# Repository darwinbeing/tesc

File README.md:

VESC – Open Source ESC
=============

This the Hardware for my open source custom ESC.

[//]: # (Image References)
[image1]: design/PNGs/VESC_6_plus_top.png "MB Front"
[image2]: design/PNGs/VESC_6_plus_bottom.png "MB Back"

## 3D views
![alt text][image1]
![alt text][image2]

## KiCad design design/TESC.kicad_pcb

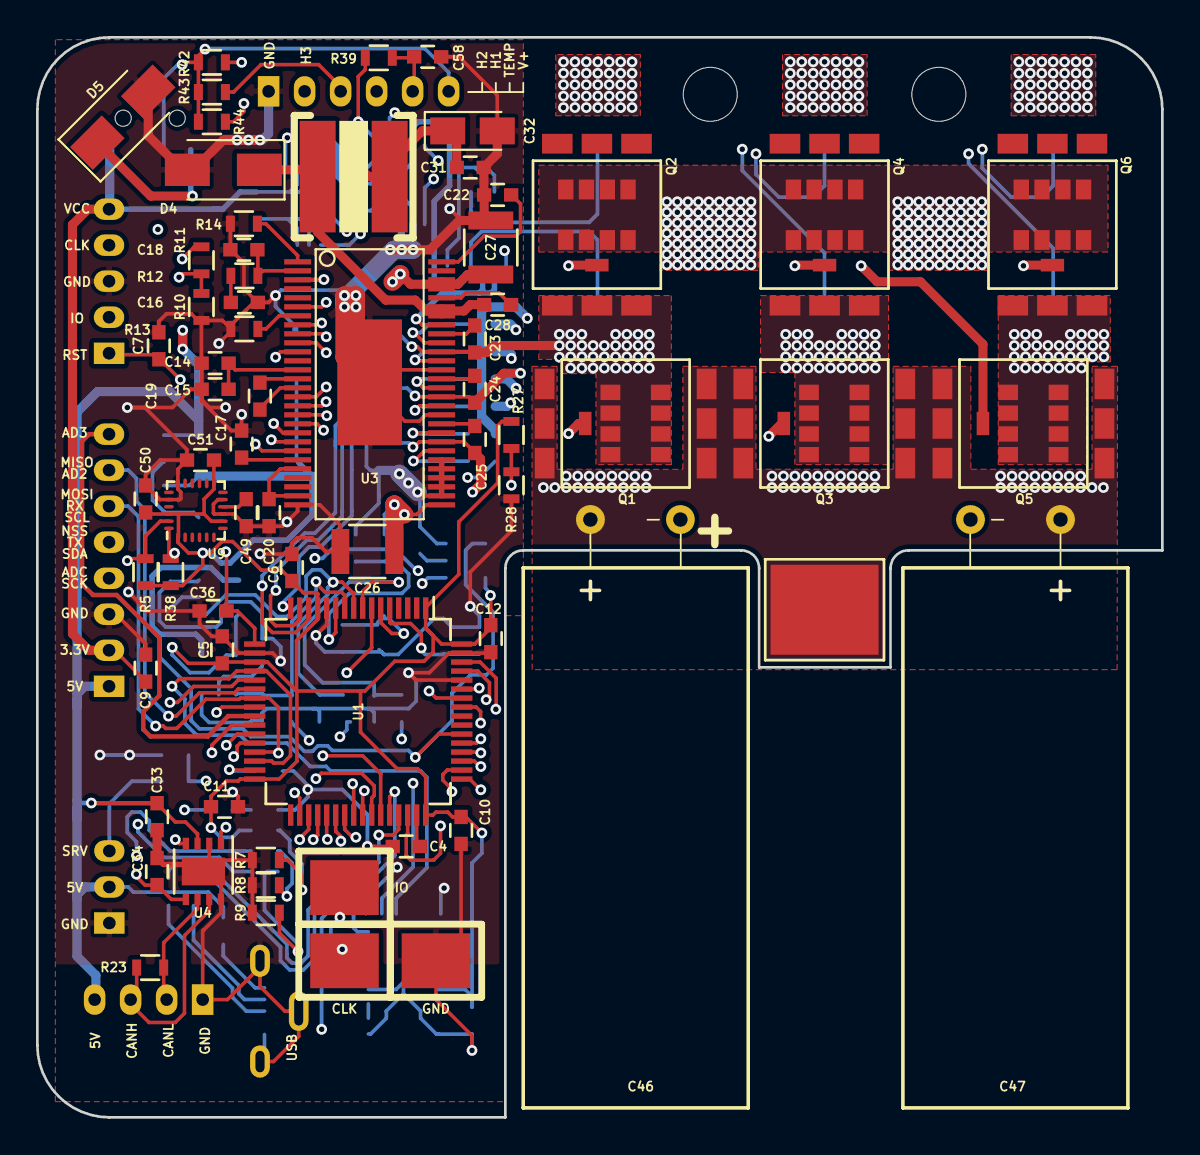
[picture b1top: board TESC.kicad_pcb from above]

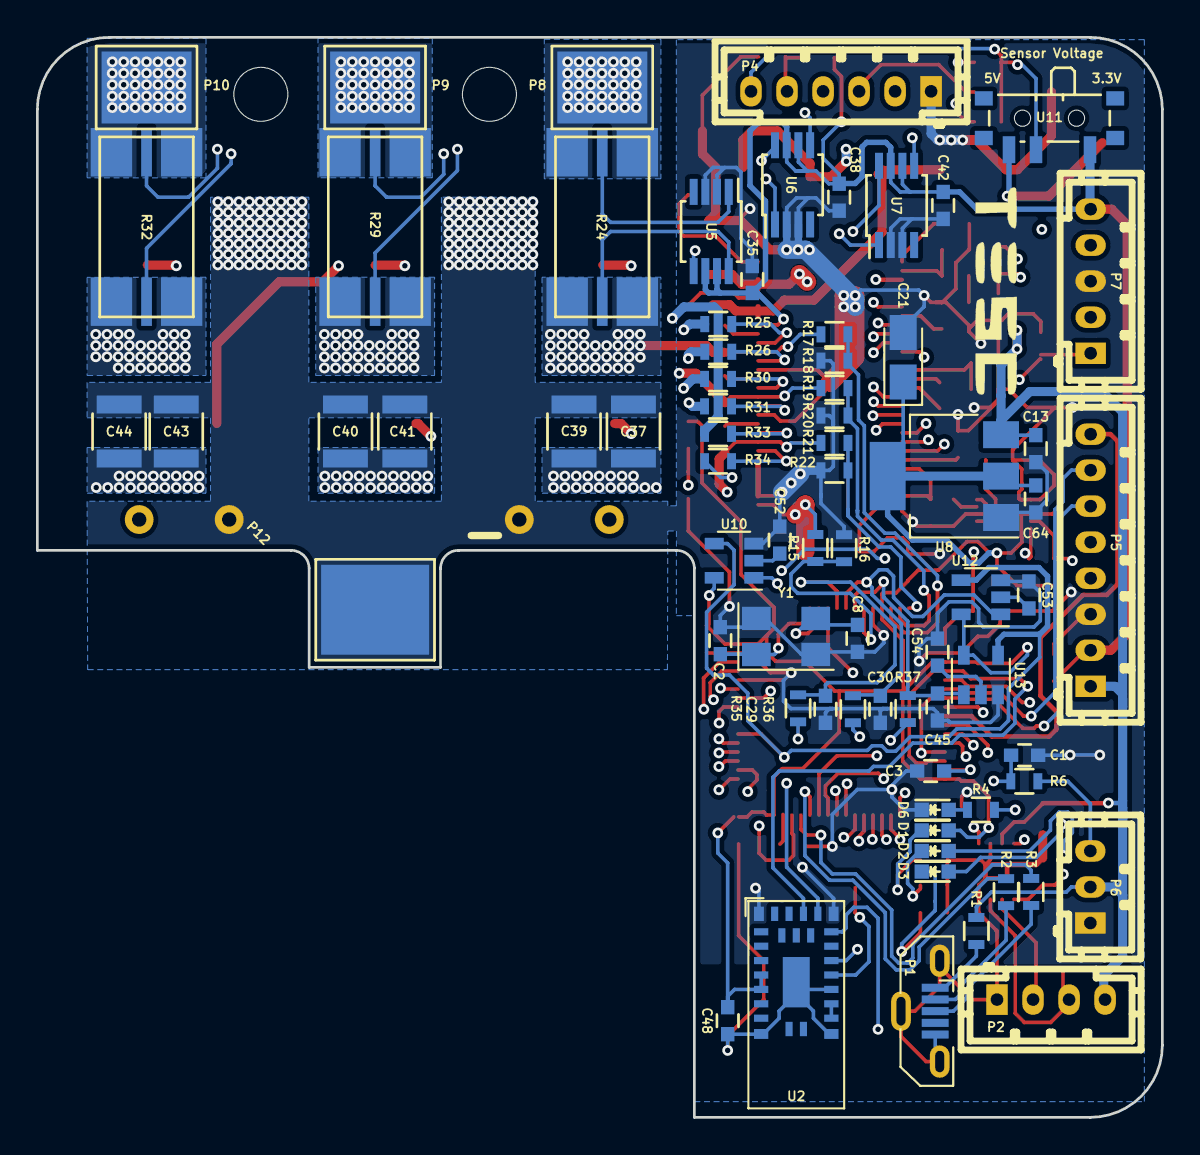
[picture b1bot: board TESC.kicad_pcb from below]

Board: 4 copper layers, 62.5 x 60.0 mm, 139 parts (72 on the bottom side), 112 nets.

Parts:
C1, C7, C28, C49, C58: 100n; C_0603
C2, C8: 15p; C_0603
C3, C4, C5, C6, C9, C10, C11, C12, C13, C14, C15, C17, C20, C31, C33, C34, C35, C36, C38, C42, C48, C50, C51, C64: 2.2u; C_0603
C16: 6.8n; C_0603
C18: 120p; C_0603
C19: 22n; C_0603
C21, C32: 100u; CP_Tantalum_Case-A_EIA-3216-18_Reflow
C22, C52, C53, C54: 15n; C_0603
C23, C24, C25: 220n; C_0603
C26, C27, C37, C39, C40, C41, C43, C44: 4.7u_100V; C_1210
C29, C30, C45: 1n; C_0603
C46, C47: 680u_63V; CP_Radial_D12.5mm_P5.00mm
CLK: CLK; 1PAD
D1: BLUE; LED_0603
D2, D6: RED; LED_0603
D3: GREEN; LED_0603
D4: DIODE; D_SMA
D5: TVS 5V; D_SMA
GND: GND; 1PAD
IO: IO; 1PAD
L2: 22u; L_Coilcraft_XAL5050
P1: USB_OTG; USB_Micro-B_Vertical_Molex-105133-0001
P2: CAN; b4b-ph-kl
P4: HALL_ENC; b6b-ph-kl
P5: COM; b8b-ph-kl
P6: SERVO; b3b-ph-kl
P7: SWD; b5b-ph-kl
P8: PH_A; 1PAD_4x5mm
P9: PH_B; 1PAD_4x5mm
P10: PH_C; 1PAD_4x5mm
P11: SUPPLY; 1PAD_6x5mm
P12: GND; 1PAD_6x5mm
Q1, Q2, Q3, Q4, Q5, Q6: IRF7749; IR-directFET_L8-Outline_Names
R1: 0R; R_0603
R2, R3: 22R; R_0603
R4, R5, R7, R35, R36, R37, R38: 1k; R_0603
R6: 100R; R_0603
R8, R9, R23: 220R; R_0603
R10: 3.3k; R_0603
R11: 18k; R_0603
R12: 15k; R_0603
R13, R28, R39: 10k; R_0603
R14: 220k; R_0603
R15, R17, R19, R21: 39k; R_0603
R16, R18, R20, R22, R42, R43, R44: 2k2; R_0603
R24, R29, R32: 0.0005R; SHUNT_CSS2H-3920
R25, R26, R30, R31, R33, R34: 4.7R; R_0603
R27: NTC 10k; R_0603
U1: STM32F40X_LQFP64; STM32F4x5RG
U2: NRF51822-TY_EYSGJNZWY; Taiyo-Yuden_EYSGJNZWY
U3: DRV8301; TSSOP-56-PP
U4: TJA1051TK3; DFN-8-1EP_3x3mm_Pitch0.65mm
U5, U6, U7: AD8418; MSOP-8_3x3mm_Pitch0.65mm
U8: TC2117; SOT-223
U9: MPU9250; QFN-24_3x3mm_Pitch0.4mm
U10, U12, U13: MC74VHC1GT66; SOT-23-5
U11: SENSOR_VOLTAGE; SW_SPDT_PCM12
Y1: 8M; Crystal_SMD_5032-4pin_5.0x3.2mm

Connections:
+5V: C13.1, C31.1, C32.1, C33.1, D5.1, L2.2, P2.4, P5.1, P6.2, R1.2, R11.2, U4.3, U8.3, U11.3
/CAN/CANH: P2.3, R23.1, U4.7
/CAN/CANL: P2.2, R23.2, U4.6
/DRV8301/CS: U1.40, U3.8
/DRV8301/EN_GATE: U1.57, U3.16
/DRV8301/FAULT: U1.59, U3.6
/DRV8301/GH_A: R25.2, U3.47
/DRV8301/GH_B: R30.2, U3.42
/DRV8301/GH_C: R33.2, U3.37
/DRV8301/GL_A: R26.2, U3.45
/DRV8301/GL_B: R31.2, U3.40
/DRV8301/GL_C: R34.2, U3.35
/DRV8301/INL_A: U1.34, U3.18
/DRV8301/INL_B: U1.35, U3.20
/DRV8301/INL_C: U1.36, U3.22
/DRV8301/SCLK: U1.51, U3.11
/DRV8301/SDI: U1.53, U3.9
/DRV8301/SDO: U1.52, U3.10
/DRV8301/SENS_A: R17.1, R18.1, U1.14
/DRV8301/SENS_B: R19.1, R20.1, U1.15
/DRV8301/SENS_C: R21.1, R22.1, U1.16
/DRV8301/SH_A: C23.2, Q1.S, Q2.D, R17.2, R24.2, U3.46
/DRV8301/SH_B: C24.2, Q3.S, Q4.D, R19.2, R29.2, U3.41
/DRV8301/SH_C: C25.2, Q5.S, Q6.D, R21.2, R32.2, U3.36
/MCU/ADC_15: P5.8, U1.25
/MCU/ADC_TEMP: C36.1, R27.2, R28.1, U1.17
/MCU/AI_IN: R15.1, R16.1, U1.11
/MCU/CAN_RX: U1.61, U4.4
/MCU/CAN_TX: U1.62, U4.1
/MCU/CURRENT_1: C29.1, R35.2, U1.8, U10.1
/MCU/CURRENT_2: C30.1, R36.2, U1.9, U12.1
/MCU/CURRENT_3: C45.1, R37.2, U1.10, U13.1
/MCU/H1: U1.41, U3.17
/MCU/H2: U1.42, U3.19
/MCU/H3: U1.43, U3.21
/MCU/HALL_1: P4.4, R42.1, U1.37
/MCU/HALL_2: P4.3, R43.1, U1.38
/MCU/HALL_3: P4.2, R44.1, U1.39
/MCU/LED_GREEN: D3.2, U1.26
/MCU/LED_RED: D2.2, U1.27
/MCU/MISO_ADC_EXT2: P5.7, U1.22
/MCU/NRST: C7.1, P7.1, U1.7
/MCU/PA15: R5.1, U1.50, U9.23
/MCU/PB2: R38.1, U1.28, U9.24
/MCU/RX_SDA_NSS: P5.5, U1.20, U1.30, U2.22
/MCU/SCK_ADC_EXT: P5.4, U1.21
/MCU/SERVO: C1.1, R6.1, U1.58
/MCU/SWCLK: P7.4, U1.49
/MCU/SWDIO: P7.2, U1.46
/MCU/TEMP_MOTOR: C58.1, P4.5, R39.1, U1.24
/MCU/TX_SCL_MOSI: P5.6, U1.23, U1.29, U2.21
/MCU/USB_DM: R2.1, U1.44
/MCU/USB_DP: R3.1, U1.45
/Power/CURR_FILTER: U1.54, U10.4, U12.4, U13.4
/Power/C_A: R35.1, U5.5
/Power/C_B: R36.1, U6.5
/Power/C_C: R37.1, U7.5
GND: C1.2, C2.1, C3.1, C4.1, C5.2, C6.2, C7.2, C8.1, C9.2, C10.2, C11.2, C12.2, C13.2, C14.2, C15.2, C16.1, C17.2, C18.1, C20.2, C21.2, C22.2, C26.2, C27.2, C29.2, C30.2, C31.2, C32.2, C33.2, C34.2, C35.2, C36.2, C37.2, C38.2, C39.2, C40.2, C41.2, C42.2, C43.2, C44.2, C45.2, C46.2, C47.2, C48.2, C49.1, C50.1, C51.1, C52.2, C53.2, C54.2, C58.2, C64.2, D4.2, D5.2, D6.1, GND.1, P1.5, P1.6, P2.1, P4.1, P5.3, P6.1, P7.3, P12.1, Q2.S, Q4.S, Q6.S, R7.1, R8.1, R9.1, R10.1, R13.1, R14.1, R16.2, R18.2, R20.2, R22.2, R28.2, U1.12, U1.18, U1.60, U1.63, U2.1, U2.9, U2.12, U2.15, U2.20, U2.28, U3.28, U3.30, U3.31, U3.32, U3.33, U3.34, U3.39, U3.44, U3.57, U4.2, U4.8, U4.9, U5.2, U5.3, U6.2, U6.3, U7.2, U7.3, U8.1, U9.9, U9.11, U9.18, U9.20, U10.3, U12.3, U13.3, Y1.2, Y1.4
unnamed: C2.2, U1.5, Y1.1
unnamed: C3.2, U1.31
unnamed: C4.2, U1.47
unnamed: C8.2, U1.6, Y1.3
unnamed: C14.1, C15.1, U3.13
unnamed: C16.2, R12.1
unnamed: C17.1, U3.23
unnamed: C18.2, R12.2, U3.2
unnamed: C19.1, U3.14
unnamed: C19.2, U3.15
unnamed: C20.1, U3.24, U3.27
unnamed: C22.1, U3.56
unnamed: C23.1, U3.48
unnamed: C24.1, U3.43
unnamed: C25.1, U3.38
unnamed: C28.1, U3.52
unnamed: C28.2, D4.1, L2.1, U3.50, U3.51
unnamed: C49.2, U9.10
unnamed: C52.1, U10.2
unnamed: C53.1, U12.2
unnamed: C54.1, U13.2
unnamed: D1.1, R7.2
unnamed: D2.1, R8.2
unnamed: D3.1, R9.2
unnamed: D6.2, R4.1
unnamed: IO.1, U2.16
unnamed: CLK.1, U2.17
unnamed: P1.1, R1.1
unnamed: P1.2, R2.2
unnamed: P1.3, R3.2
unnamed: P4.6, R42.2, R43.2, R44.2, U11.2
unnamed: P6.3, R6.2
unnamed: P8.1, R24.1
unnamed: P9.1, R29.1
unnamed: P10.1, R32.1
unnamed: Q1.G, R25.1
unnamed: Q2.G, R26.1
unnamed: Q3.G, R30.1
unnamed: Q4.G, R31.1
unnamed: Q5.G, R33.1
unnamed: Q6.G, R34.1
unnamed: R4.2, U2.19
unnamed: R10.2, R11.1, U3.3
unnamed: R13.2, U3.7
unnamed: R14.2, U3.1
unnamed: R24.3, U5.1
unnamed: R24.4, U5.8
unnamed: R29.3, U6.1
unnamed: R29.4, U6.8
unnamed: R32.3, U7.1
unnamed: R32.4, U7.8
unnamed: U2.13, U2.14
SUPPLY: C26.1, C27.1, C37.1, C39.1, C40.1, C41.1, C43.1, C44.1, C46.1, C47.1, P11.1, Q1.D, Q3.D, Q5.D, R15.2, U3.29, U3.53, U3.54
VCC: C5.1, C6.1, C9.1, C10.1, C11.1, C12.1, C21.1, C34.1, C35.1, C38.1, C42.1, C48.1, C50.2, C51.2, C64.1, D1.2, P5.2, P7.5, R5.2, R27.1, R38.2, R39.2, U1.1, U1.13, U1.19, U1.32, U1.48, U1.64, U2.5, U2.6, U3.49, U4.5, U5.6, U5.7, U6.6, U6.7, U7.6, U7.7, U8.2, U8.4, U9.1, U9.8, U9.13, U9.22, U10.5, U11.1, U12.5, U13.5

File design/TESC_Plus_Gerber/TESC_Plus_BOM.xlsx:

Title |  | TESC 6.6
Total Parts |  | 136
Total Unique Parts |  | 55
No | Ref | Qty | Value | Footprint | Description | Part Number | Note
1.0 | C1 C7 C28 C49 C58 | 5.0 | 100n | C_0603 | CAP 0.1uF 50V 0603 5% X7R | C0603X104J5RACTU
2.0 | C2 C8 | 2.0 | 15p | C_0603 | CAP 15pF 50V 0603 5% C0G | 06035A150GAT2A
3.0 | C3 C4 C5 C6 C9 C10 C11 C12 C13 C14 C15 C17 C20 C31 C33 C34 C35 C36 C38 C42 C48 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 | 24.0 | 2.2u | C_0603 | CAP 2.2uF 16V 0603 10% X5R | C1608X5R1C225K080AB
4.0 | C16 | 1.0 | 6.8n | C_0603 | CAP 6800pF 50V 0603 10% X7R | GCD188R71H682KA01D
5.0 | C18 | 1.0 | 120p | C_0603 | CAP 120pF 50V 0603 5% C0G | 06035A121JAT2A
6.0 | C19 | 1.0 | 22n | C_0603 | CAP 0.022uF 50V 0603 10% X7R | GCM188R71H223KA37J
7.0 | C21 C32 | 2.0 | 100u | CP_Tantalum_Case-A_EIA-3216-18_Reflow | CAP 100uF 6.3V 1206 10% 1206 | TLJA107M006R0500
8.0 | C22 C52 C53 C54 | 4.0 | 15n | C_0603 | CAP 0.015uF 50V 0603 10% X7R | GCM188R71H153KA37D
9.0 | C23 C24 C25 | 3.0 | 220n | C_0603 | CAP 0.22uF 25V 0603 10% X7R | GCM188R71E224KA55D
10.0 | C26 C27 C37 C39 C40 C41 C43 C44 | 8.0 | 4.7u_100V | C_1210 | CAP 4.7uF 100V 1210 10% X7S | 12101C475K4T2A
11.0 | C29 C30 C45 | 3.0 | 1n | C_0603 | CAP 1nF 50V 0603 5% X7R | 06035C102JAT2A
12.0 | C46 C47 | 2.0 | 680u_63V | C_0603 | CAP 680uF 63V 20% | EKZN630ELL681MK30S
13.0 | D1 | 1.0 | BLUE | LED_0603 | LED Blue | VLMB1300-GS08
14.0 | D2 D6 | 2.0 | RED | LED_0603 | LED Red | VLMS1300-GS08
15.0 | D3 | 1.0 | GREEN | LED_0603 | LED Green | VLMTG1300-GS08
16.0 | D4 | 1.0 | DIODE | D_SMA | Schottky Diodes & Rectifiers 2.0 Amp 60 Volt | PMEG6020ER,115
17.0 | D5 | 1.0 | TVS 5V | D_SMA | TVS Diodes 5V | SMAJ5.0A
18.0 | L2 | 1.0 | 22u | L_Coilcraft_XAL5050 | IND 22uH 3.4A 20% | XAL5050-223MEC
19.0 | P1 | 1.0 | USB_OTG | USB_Micro-B_Vertical_Molex-105133-0001 | USB Connectors MICRO VERTICAL | 1.051330001E9
20.0 | P2 | 1.0 | CAN | b4b-ph-kl | Micro-JST 4PIN 2mm | B4B-PH-K-S (LF)(SN)
21.0 | P4 | 1.0 | HALL_ENC | b6b-ph-kl | Micro-JST 6PIN 2mm | B6B-PH-K-S (LF)(SN)
22.0 | P5 | 1.0 | COM | b8b-ph-kl | Micro-JST 8PIN 2mm | B8B-PH-K-S (LF)(SN)
23.0 | P6 | 1.0 | SERVO | b3b-ph-kl | Micro-JST 3PIN 2mm | B3B-PH-K-S (LF)(SN)
24.0 | P7 | 1.0 | SWD | b5b-ph-kl | Micro-JST 5PIN 2mm | B5B-PH-K-S (LF)(SN)
25.0 | P8 | 1.0 | PH_A | 1PAD_4x5mm | Motor Cable
26.0 | P9 | 1.0 | PH_B | 1PAD_4x5mm | Motor Cable
27.0 | P10 | 1.0 | PH_C | 1PAD_4x5mm | Motor Cable
28.0 | P11 | 1.0 | SUPPLY | 1PAD_6x5mm | RED Silicon Cable
29.0 | P12 | 1.0 | GND | 1PAD_6x5mm | BLACK Silicon Cable
30.0 | Q1 Q2 Q3 Q4 Q5 Q6 | 6.0 | IRF7749 | DirectFET_L8 | MOSFET 60V | IRF7749L1TRPBF
31.0 | R1 | 1.0 | 0R | R_0603 | RES 0 OHM 50V 0603 5% 1/10W | CR0603-J/-000ELF | DO NOT MOUNT
32.0 | R2 R3 | 2.0 | 22R | R_0603 | SMD 22 ohm 1% | CR0603-FX-22R0ELF
33.0 | R4 R5 R7 R35 R36 R37 R38 | 7.0 | 1k | R_0603 | SMD 1K 1% 1/10W | CR0603-FX-1001ELF
34.0 | R6 | 1.0 | 100R | R_0603 | SMD 100ohm 1% 1/10W | CR0603-FX-1000ELF
35.0 | R8 R9 R23 | 3.0 | 220R | R_0603 | SMD 220 ohm 1% | CR0603-FX-2200ELF
36.0 | R10 | 1.0 | 3.3k | R_0603 | SMD 3.3KOHM 1/10WATT 1% | CR0603-FX-3301ELF
37.0 | R11 | 1.0 | 18k | R_0603 | SMD 1/10watt 18Kohms 1% | CR0603-FX-1802ELF
38.0 | R12 | 1.0 | 15k | R_0603 | SMD 1/10watt 15Kohms 1% | CR0603-FX-1502ELF
39.0 | R13 R28 R39 | 3.0 | 10k | R_0603 | SMD 10K 1% 1/10W | CR0603-FX-1002ELF
40.0 | R14 | 1.0 | 220k | R_0603 | SMD 0603 220Kohms 1% | CR0603-FX-2203ELF
41.0 | R15 R17 R19 R21 | 4.0 | 39k | R_0603 | SMD 39K ohm 1% | CR0603-FX-3902ELF
42.0 | R16 R18 R20 R22 R42 R43 R44 | 7.0 | 2k2 | R_0603 | SMD 2.2K 1% 1/10W | CR0603-FX-2201ELF
43.0 | R24 R29 R32 | 3.0 | 0.0005R | SHUNT_CSS2H-3920 | SMD 0.5mOHMS 5W 1% | LRMAP3920B-R0005FT
44.0 | R25 R26 R30 R31 R33 R34 | 6.0 | 4.7R | R_0603 | SMD 1/10watt 4.7ohms 1% | CRCW06034R70FKEA
45.0 | R27 | 1.0 | NTC 10k | R_0603 | NTC Thermistors 10K OHM 1% | NCP18XH103F03RB
46.0 | U1 | 1.0 | STM32F40X_LQFP64 | STM32F4x5RG | MCU ARM M4 1024 LQFP-64 | STM32F405RGT6
47.0 | U2 | 1.0 | NRF51822-TY_EYSGJNZWY | Taiyo-Yuden_EYSGJNZWY | BLE | EYSGJNZWY
48.0 | U3 | 1.0 | DRV8301 | TSSOP-56-PP | MOSFET Driver DRV8301 | DRV8301DCA
49.0 | U4 | 1.0 | TJA1051TK3 | DFN-8-1EP_3x3mm_Pitch0.65mm | CAN TRANSCEIVER | TJA1051TK/3,118
50.0 | U5 U6 U7 | 3.0 | AD8418 | MSOP-8_3x3mm_Pitch0.65mm | Current Sense Amplifiers | AD8418AWBRMZ
51.0 | U8 | 1.0 | TC2117 | SOT-223 | LDO Voltage Regulators | TC2117-3.3VDBTR
52.0 | U9 | 1.0 | MPU9250 | QFN-24_3x3mm_Pitch0.4mm | IMUs - Inertial Measurement Units | MPU-9250
53.0 | U10 U12 U13 | 3.0 | MC74VHC1GT66 | SOT-23-5 | Analog Switch | M74VHC1GT66DTT1G
54.0 | U11 | 1.0 | SENSOR_VOLTAGE | SW_SPDT_PCM12 | Slide Switches SPDT ON-ON | PCM12SMTR
55.0 | Y1 | 1.0 | 8M | Crystal_SMD_5032_4Pads | Crystals 8.0MHz 10pf 10ppm | ABM3B-8.000MHZ-10-1-U-T

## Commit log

2018-04-03 initial commit -m
2018-04-07 dimension 60X60
2018-04-13 Cleanup Tracks and Vias
2018-04-21 Prepare version 1.0
2018-04-27 TESC 1.0
2018-04-30 TESC 1.1
2018-05-01 Add polarity direction silk screen
2018-05-01 TESC 1.2
2018-05-04 TESC 1.3
2018-05-05 TESC 1.4
2018-05-05 Make Loops Small
2018-05-06 Add manf# field
2018-05-06 TESC Release
2018-05-06 Change silk screen
2018-05-06 Optimize copper ground pour
2018-05-07 Change U11 silk screen
2018-05-07 Optimize trace
2018-05-08 SHUNT_CSS2H-3920: add silk screen
2018-05-08 Add mpu9250 impl
2018-05-08 Regenerate Gerber
2018-05-08 MPU9250: add part number field
2018-05-10 Change all via size
2018-05-11 Add TESC_HandSoldering.xlsx
2018-05-13 Add CSS2H-3920 3D model
2018-05-14 Optimize track
2018-05-14 Optimize silks
2018-05-17 Update silk screen
2018-05-20 Optimize silk screen & track
2018-05-21 Add visual diff scripts Kicad on OSX/Windows doesn't support python api
2018-05-21 Update scripts
2018-05-21 Update track, copper pour
2018-05-21 Optimize silk screen
2018-05-23 Add Gerber.zip
2018-05-27 Generate gerber files
2018-05-28 Add gen_fab.py
2018-05-28 Update silks, re-generate gerber files
2018-05-28 Add Silks pdf files
2018-05-28 Update silks
2018-05-28 Optimize layout
2018-05-28 Optimize layout, generate gerber files
2018-05-29 Zip gerber files
2018-05-29 Add gerber zip file
2018-05-29 Update hand soldering pdf
2018-06-02 Optimize track, rearrange NRF module
2018-06-15 Add OpenSCAD Tutorial
2018-06-18 Update Project Enclosure,VESC Case/Lid
2018-07-10 Add 3D STEP model
2018-07-10 Update 3D STEP model
2018-07-15 Update PCB
2018-10-23 Change layout
2019-11-12 Support KiCad 5.1.4
2019-11-13 Improve layout
2019-11-13 Improvements
2019-11-15 Load KiCad 4.0.7 schematic symbols, footprints & 3D models
2019-11-15 Add ICM-20948 support
2019-11-15 Revert "Add ICM-20948 support"
    This reverts commit 6973a9f76e2e1207f1c7879789cf7605503054ef.
2019-11-16 Generate Gerber and Drill files from KiCad to produce the PCB boards
2019-11-17 Design VESC6 plus sch done
2019-11-17 Add .gitignore
2019-11-17 BLE layout update
2019-11-17 Cleanup Tracks
2019-11-17 Update layout
2019-11-18 Lock mounting hole footprint, modify the pad name of directFET
2019-11-18 Update MC74VHC1GT66
2019-11-18 assign component footprint
2019-11-19 Update footprints
2019-11-19 remove VESC_6.net VESC_6.xml
2019-11-21 Update part number
2019-11-21 remove VESC_6.xml
2019-11-23 Update LEDs silkscreen
2019-12-03 Update Fabrication Attributes
2019-12-07 Change Clearance of copper pours of net SUPPLY
2019-12-07 remove text
2019-12-07 Cleanup silkscreen
2019-12-08 Add pcbnew script
2019-12-11 Enable MPU-9150
2019-12-12 remove VESC_6.net
2019-12-16 Revert "Update layout"
    This reverts commit 6f6561b38768be4a724b66136c09b621815d8cf7.
2019-12-17 CSS2H-3920: Add courtyard
2019-12-17 Revert "Update layout"
    This reverts commit 45bea8e93f9dc7d3e1b9c4a0c7db77cd9d0da43e.
2019-12-18 GenerateGerber files in RS-274x format
2019-12-18 remove .DS_Store
2019-12-18 Generate Gerber and drill files in RS-274x format
2019-12-21 Remove IO/CLK/GND Paste
2019-12-21 Optimize INL_C track
2019-12-21 Update C2/C8/C51/C52 BOM(06035A150GAT2A)
2019-12-25 Change Mounting Hole Attribute
2019-12-25 Correct Mounting Hole Attribute
2019-12-28 tent vias
2020-03-15 Update silkscreen
2020-05-03 rename files
2020-05-03 Remove unused files
2020-05-27 Add LEO MOTION logo
2024-06-09 Upload 3D images
2024-06-09 Upload VESC 6 3D images
2024-06-09 Upload VESC 6 Plus 3D images
